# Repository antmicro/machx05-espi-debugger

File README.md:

# MachXO5 eSPI Debugger

Copyright (c) 2026 [Antmicro](https://www.antmicro.com)

## Overview

This project contains open hardware design files for an FPGA-based debug board built around the Lattice MachXO5-NX FPGA.
The board is designed to aid the process of development, bring-up and integration of eSPI-based connections to Data Center Secure Control Modules (DC-SCMs).
It provides USB-accessible UART and JTAG interfaces and a Port 80 status display, enabling development, testing and debugging of eSPI communication before integration into a target server platform.
This project includes only PCB design files - as dedicated bitstream needs to be generated for the on-board Lattice FPGA in order to make it work.
The PCB design files were prepared in KiCad 10.x.

## Key features

* Lattice [MachXO5-NX LFMXO5-25-7BBG400C](https://www.latticesemi.com/en/Products/FPGAandCPLD/MachXO5-NX) FPGA
* Generic 0.1 inch pinhead connector for interfacing with HPM subsystem
* USB-C port with FTDI FT2232H USB interface bridge
* UART and JTAG interfaces accessible from the USB interface bridge
* Port 80 status display with LED indicators
* 125 MHz on-board clock source
* 62 x 87 mm (2.44 x 3.42 inch) PCB outline

## Project structure

The main directory contains KiCad PCB project files, the LICENSE, and this README, and the img directory contains graphics for this README.

## License

This project is licensed under the [Apache-2.0](LICENSE) license.

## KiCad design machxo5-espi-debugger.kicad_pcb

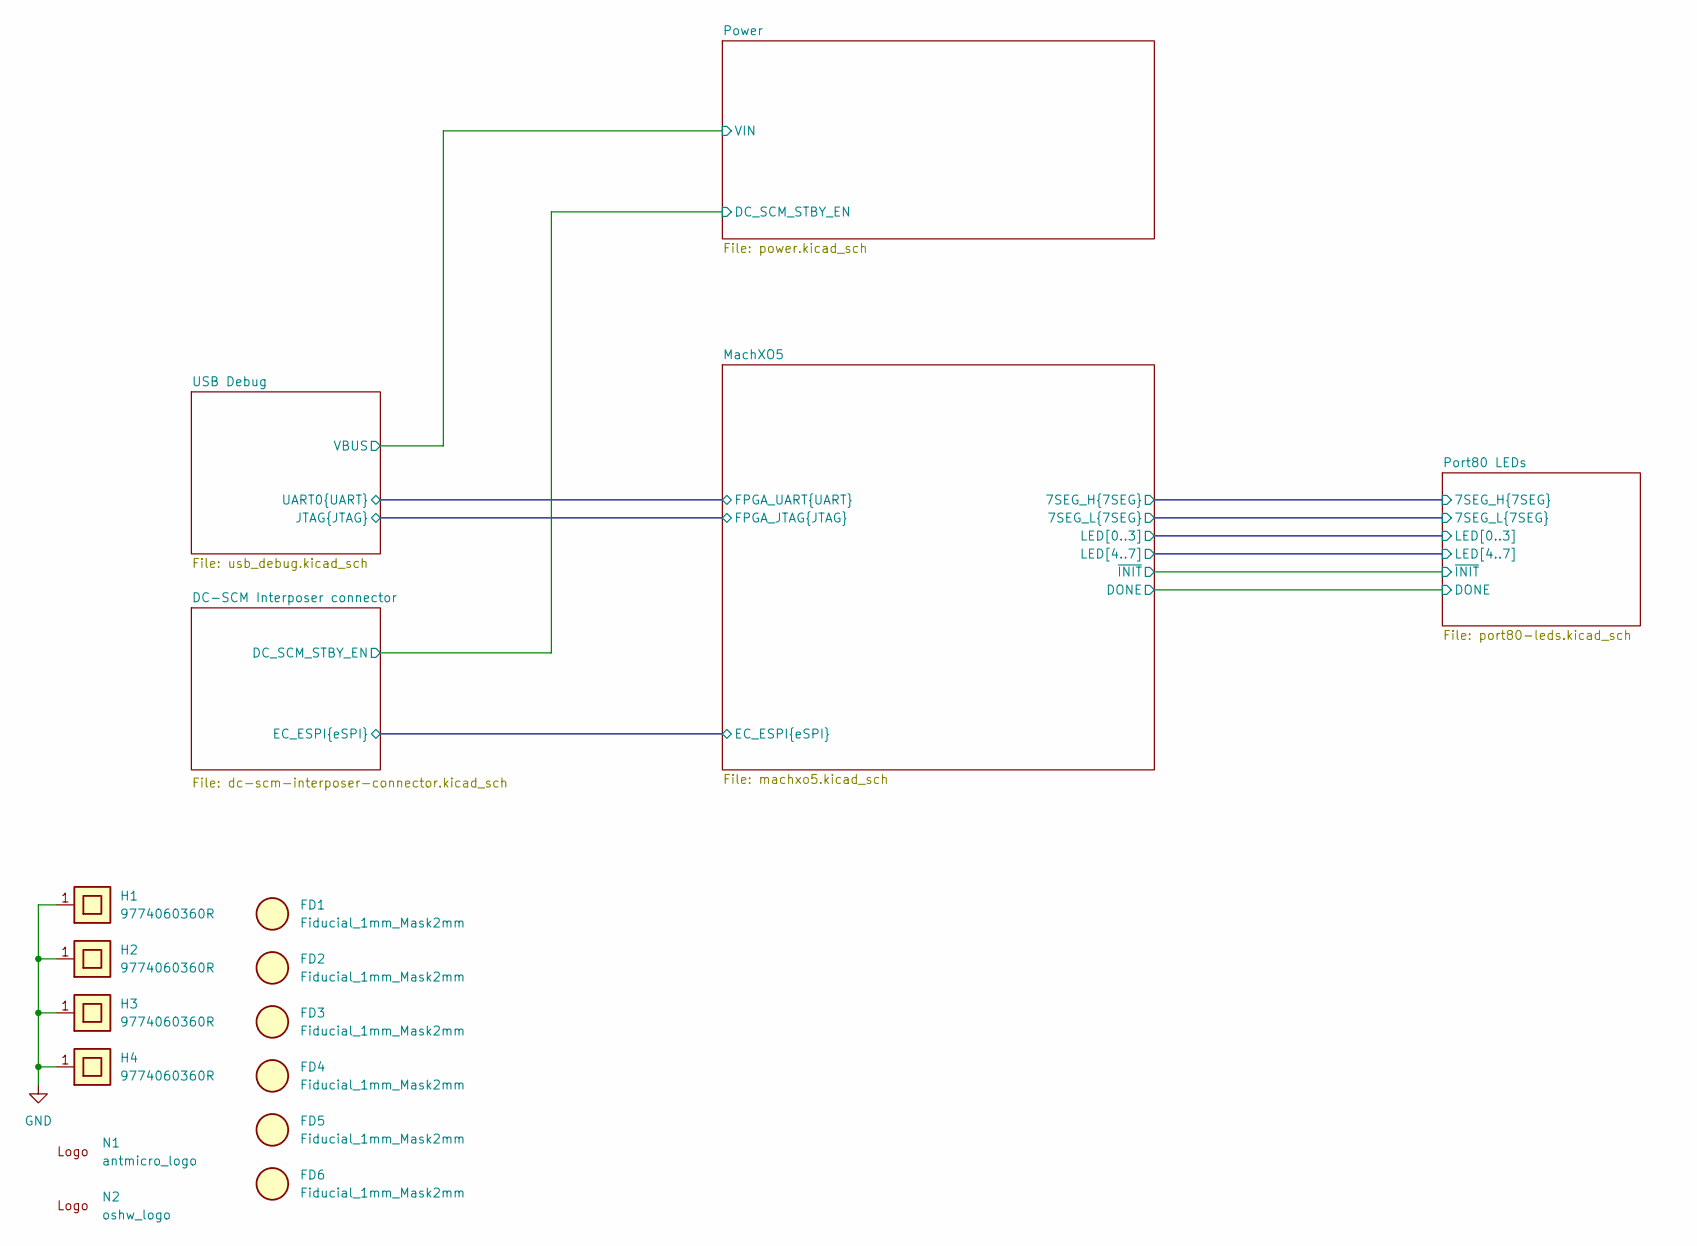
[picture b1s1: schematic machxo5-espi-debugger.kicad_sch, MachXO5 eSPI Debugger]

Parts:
FD1, FD2, FD3, FD4, FD5, FD6: Fiducial_1mm_Mask2mm
H1, H2, H3, H4: Spacer_Drill4.4mm_H6mm_9774060360R; MPN 9774060360R
N1: antmicro_logo; antmicro-logo_scaled_12mm
N2: oshw_logo; oshw-logo

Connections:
GND: H1.1, H2.1, H3.1, H4.1; also elsewhere on the board

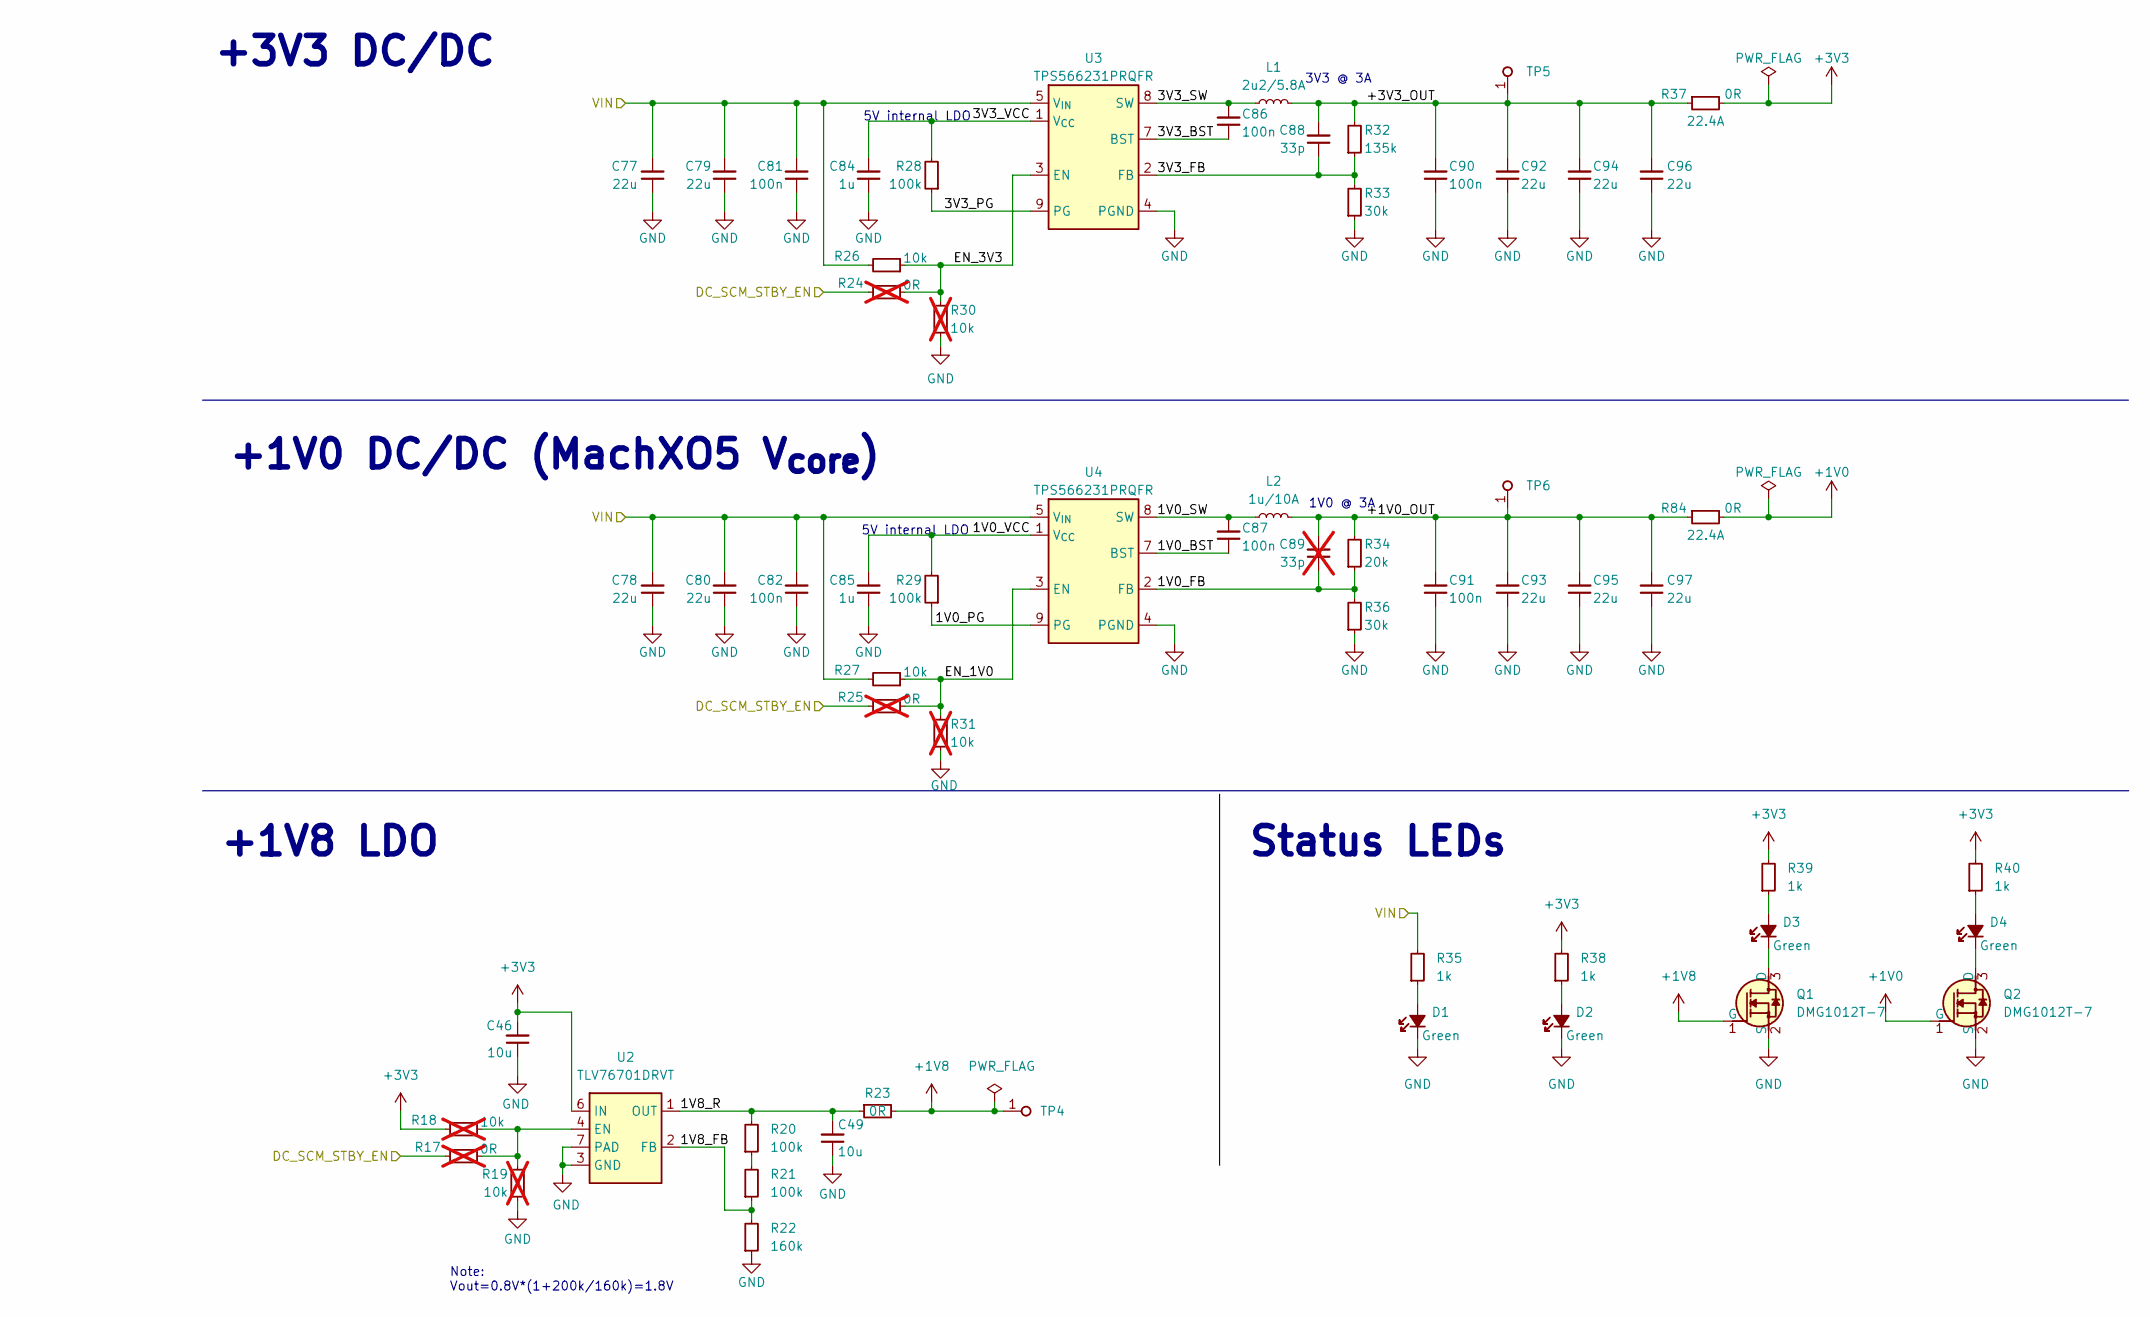
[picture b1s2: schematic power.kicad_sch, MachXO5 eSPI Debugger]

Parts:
C46, C49: C_10u_10V_0402; C_0402_1005Metric; Voltage 10V; MPN GRM155R61A106ME11D
C77, C78, C79, C80, C92, C93, C94, C95, C96, C97: C_22u_16V_0603; C_0603_1608Metric_EIA; Voltage 16V; MPN CL10A226MO7JZNC
C81, C82, C86, C87, C90, C91: C_100n_0402; C_0402_1005Metric; Voltage 50V; MPN GRM155R61H104KE14D
C84, C85: C_1u_25V_0402; C_0402_1005Metric; Voltage 25V; MPN GRM155R61E105KE11J
C88: C_33p_0402; C_0402_1005Metric; MPN 04025A330FAT2A
C89: C_33p_0402; C_0402_1005Metric; MPN 04025A330FAT2A; not fitted
D1, D2, D3, D4: LED_G_0603_LTST-C190GKT; LED_0603_1608Metric_G; MPN LTST-C190GKT
L1: L_2u2_5.8A_WE-PMFI-35329222; L_WE-PMFI-353220; MPN 74479335329222
L2: L_1u_10A_Bourns-SRP4021HMT; L_Bourns-SRP4021HMT; MPN SRP4021HMT-1R0M
Q1, Q2: DMG1012T-7; SOT-523; MPN DMG1012T-7
R17, R24, R25: R_0R_0402; R_0402_1005Metric; MPN ERJ2GE0R00X; not fitted
R18, R19, R30, R31: R_10k_0402; R_0402_1005Metric; Tolerance 1%; MPN CR0402-FX-1002GLF; not fitted
R20, R21, R28, R29: R_100k_0402; R_0402_1005Metric; Tolerance 1%; MPN CR0402-FX-1003GLF
R22: R_160k_0402; R_0402_1005Metric; Tolerance 1%; MPN CR0402-FX-1603GLF
R23: R_0R_0402; R_0402_1005Metric; MPN ERJ2GE0R00X
R26, R27: R_10k_0402; R_0402_1005Metric; Tolerance 1%; MPN CR0402-FX-1002GLF
R32: R_135k_0402; R_0402_1005Metric; Tolerance 0.1%; MPN RT0805BRD07135KL
R33, R36: R_30k_0402; R_0402_1005Metric; Tolerance 1%; MPN CR0402-FX-3002GLF
R34: R_20k_0402; R_0402_1005Metric; Tolerance 1%; MPN CR0402-FX-2002GLF
R35, R38, R39, R40: R_1k_0402; R_0402_1005Metric; Tolerance 1%; MPN CR0402-FX-1001GLF
R37, R84: R_0R_22.4A_0603; R_0603_1608Metric; Tolerance template_tolerance; MPN PMR03EZPJ000
TP4, TP5, TP6: TP_0.75mm_SMD; TP_SMD_0.75mm
U2: TLV76701_WSON; WSON-6-1EP_2x2mm_P0.65mm; MPN TLV76701DRVT
U3, U4: TPS566231P; VQFN-HR-9_2x1.5mm; MPN TPS566231PRQFR

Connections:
+1V0: Q2.1 (G), R84.2; also elsewhere on the board
+1V8: Q1.1 (G), R23.2, TP4.1 (1_1); also elsewhere on the board
+3V3: C46.2, R18.2, R37.2, R38.2, R39.2, R40.2, U2.6 (IN); also elsewhere on the board
/DC-SCM Interposer connector/DC_SCM_STBY_EN: R17.1, R24.1, R25.1; also elsewhere on the board
/Power/1V0_BST: C87.1, U4.7 (BST)
/Power/1V0_FB: C89.1, R34.1, R36.2, U4.2 (FB)
/Power/1V0_PG: R29.1, U4.9 (PG)
/Power/1V0_SW: C87.2, L2.1, U4.8 (SW)
/Power/1V0_VCC: C85.2, R29.2, U4.1 (V_{CC})
/Power/1V8_FB: R21.1, R22.2, U2.2 (FB)
/Power/1V8_R: C49.2, R20.2, R23.1, U2.1 (OUT)
/Power/3V3_BST: C86.1, U3.7 (BST)
/Power/3V3_FB: C88.1, R32.1, R33.2, U3.2 (FB)
/Power/3V3_PG: R28.1, U3.9 (PG)
/Power/3V3_SW: C86.2, L1.1, U3.8 (SW)
/Power/3V3_VCC: C84.2, R28.2, U3.1 (V_{CC})
/Power/+1V0_OUT: C89.2, C91.2, C93.2, C95.2, C97.2, L2.2, R34.2, R84.1, TP6.1 (1_1)
/Power/+3V3_OUT: C88.2, C90.2, C92.2, C94.2, C96.2, L1.2, R32.2, R37.1, TP5.1 (1_1)
/Power/EN_1V0: R25.2, R27.1, R31.2, U4.3 (EN)
/Power/EN_3V3: R24.2, R26.1, R30.2, U3.3 (EN)
/Power/VIN: C77.2, C78.2, C79.2, C80.2, C81.2, C82.2, R26.2, R27.2, R35.2, U3.5 (V_{IN}), U3.6 (V_{IN}), U4.5 (V_{IN}), U4.6 (V_{IN}); also elsewhere on the board
GND: C46.1, C49.1, C77.1, C78.1, C79.1, C80.1, C81.1, C82.1, C84.1, C85.1, C90.1, C91.1, C92.1, C93.1, C94.1, C95.1, C96.1, C97.1, D1.1 (C), D2.1 (C), Q1.2 (S), Q2.2 (S), R19.1, R22.1, R30.1, R31.1, R33.1, R36.1, U2.3 (GND), U2.5 (GND), U2.7 (PAD), U3.4 (PGND), U4.4 (PGND); also elsewhere on the board
unnamed: D1.2 (A), R35.1
unnamed: D2.2 (A), R38.1
unnamed: D3.2 (A), R39.1
unnamed: D3.1 (C), Q1.3 (D)
unnamed: D4.2 (A), R40.1
unnamed: D4.1 (C), Q2.3 (D)
unnamed: R20.1, R21.2
unnamed: R17.2, R18.1, R19.2, U2.4 (EN)

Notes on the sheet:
5V internal LDO
Note: Vout=0.8V*(1+200k/160k)=1.8V
3V3 @ 3A
Status LEDs
+1V8 LDO
1V0 @ 3A
+1V0 DC/DC (MachXO5 V_{core})
+3V3 DC/DC

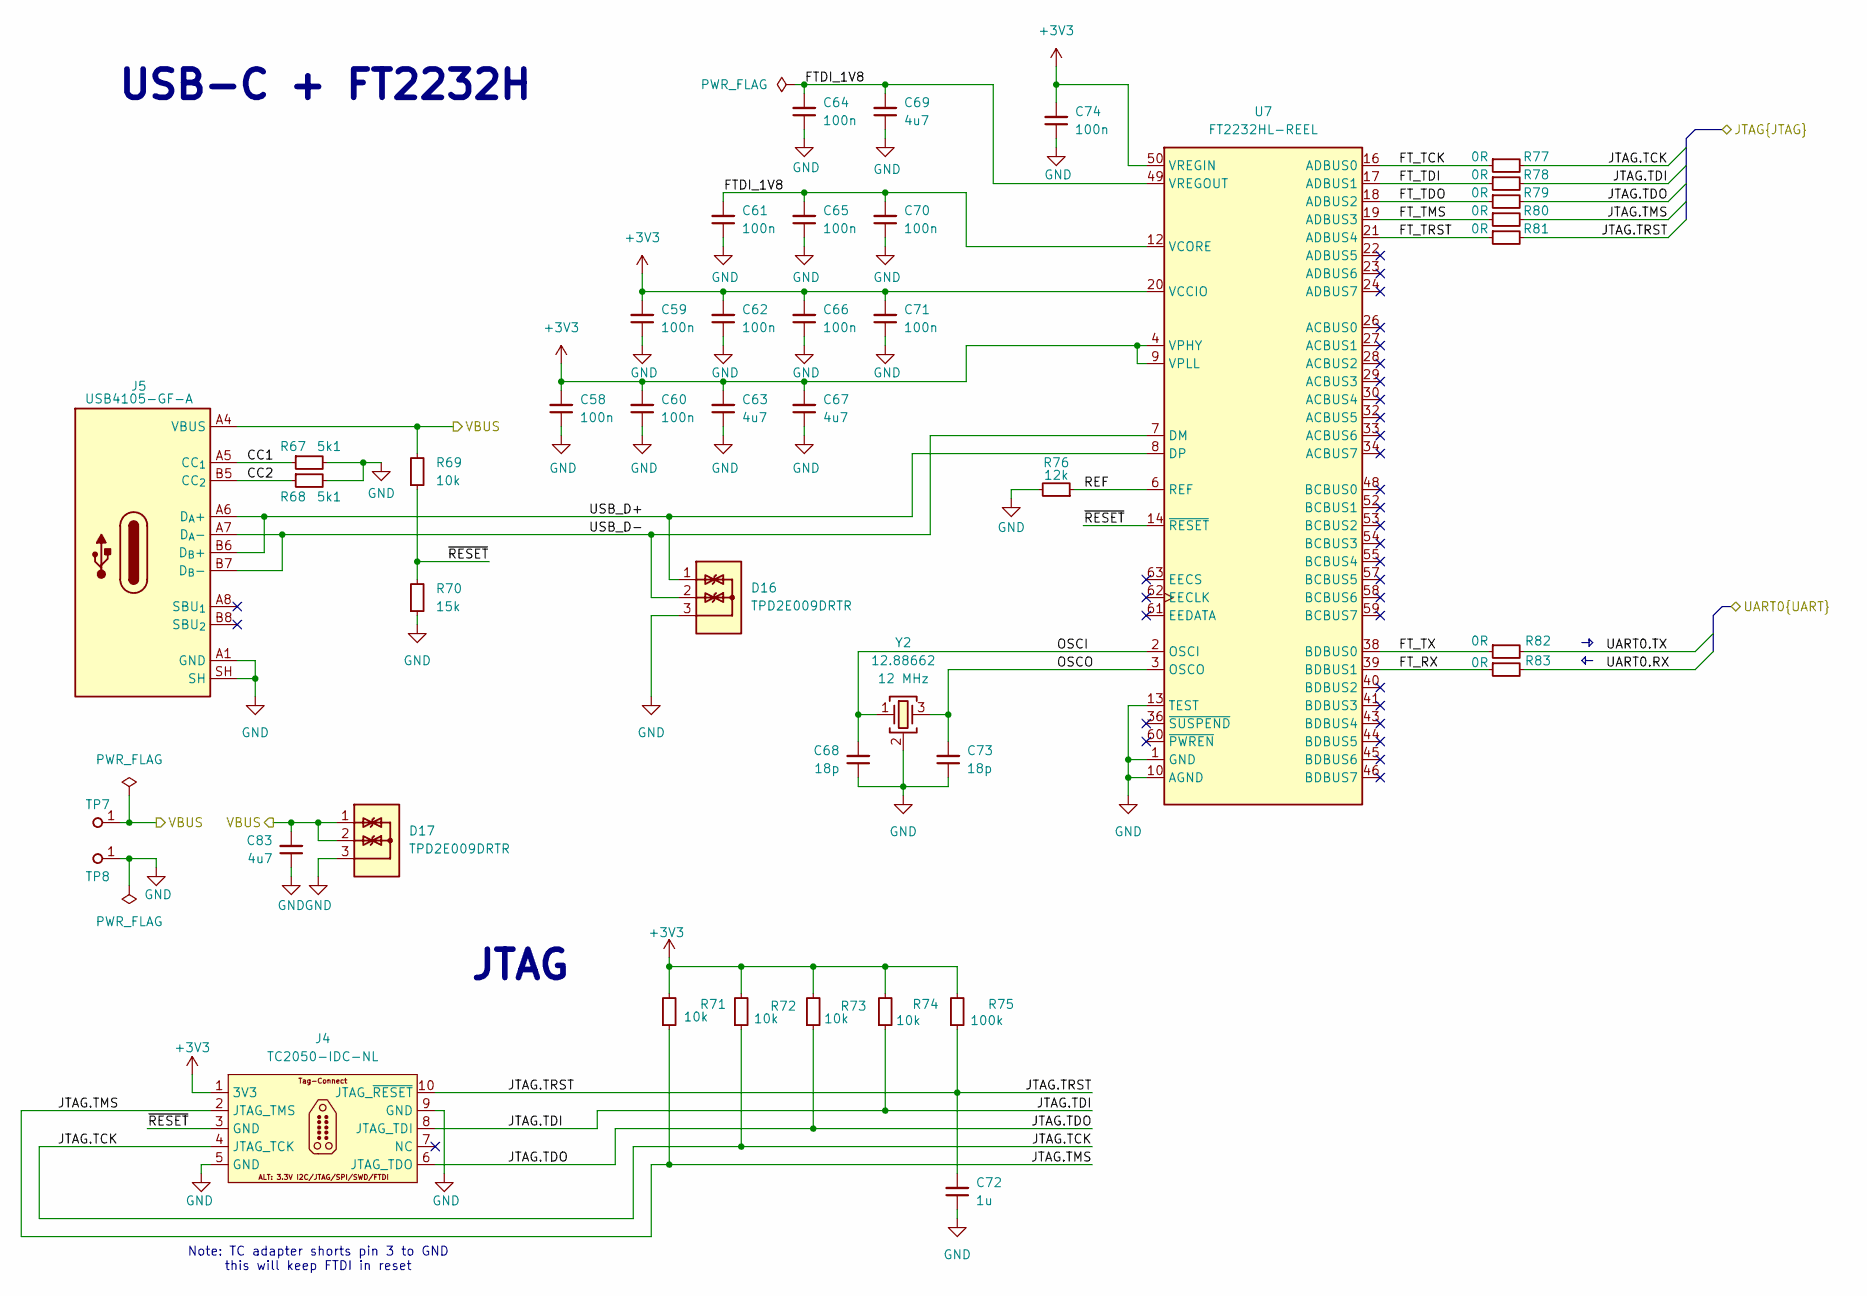
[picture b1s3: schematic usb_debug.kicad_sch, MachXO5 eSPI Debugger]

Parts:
C58, C59, C60, C61, C62, C64, C65, C66, C70, C71, C74: C_100n_16V_X7R_0402; C_0402_1005Metric; Voltage 16V; MPN C0402C104J4RAC7411
C63, C67, C69, C83: C_4u7_10V_X7T_0402; C_0402_1005Metric; Voltage 10V; MPN GRM155D71A475ME15D
C68, C73: C_18p_0402; C_0402_1005Metric; MPN CL05C180JB51PNC
C72: C_1u_0402; C_0402_1005Metric; MPN C1005X6S1A105K050BC
D16, D17: TPD2E009_SOT-9X3; SOT-723; MPN TPD2E009DRTR
J4: Tag-Connect_TC2050-IDC-NL_2x5_P1.27mm; MPN TC2050-IDC-NL
J5: USB-C_GCT_USB4105-GF-A; USB-C_Receptacle_GCT_USB4105-GF-A; MPN USB4105-GF-A
R67, R68: R_5k1_0402; R_0402_1005Metric; Tolerance 1%; MPN CR0402-FX-5101GLF
R69, R71, R72, R73, R74: R_10k_0402; R_0402_1005Metric; Tolerance 1%; MPN CR0402-FX-1002GLF
R70: R_15k_0402; R_0402_1005Metric; Tolerance 1%; MPN CR0402-FX-1502GLF
R75: R_100k_0402; R_0402_1005Metric; Tolerance 1%; MPN CR0402-FX-1003GLF
R76: R_12k_0402; R_0402_1005Metric; Tolerance 1%; MPN CR0402-FX-1202GLF
R77, R78, R79, R80, R81, R82, R83: R_0R_0402; R_0402_1005Metric; MPN ERJ2GE0R00X
TP7, TP8: TP_1mm_SMD; TP_SMD_1mm
U7: FT2232HL-REEL; LQFP-64_10x10mm_P0.5mm; MPN FT2232HL-REEL
Y2: Resonator_12MHz_KX-7; Resonator_SMD_Geyer_KX-7_3.2x2.5x0.8mm; MPN 12.88662

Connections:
+3V3: C58.2, C59.2, C60.2, C62.2, C63.2, C66.2, C67.2, C71.2, C74.2, J4.1, R71.2, R72.2, R73.2, R74.2, R75.2, U7.4 (VPHY), U7.9 (VPLL), U7.20 (VCCIO), U7.31 (VCCIO), U7.42 (VCCIO), U7.50 (VREGIN), U7.56 (VCCIO); also elsewhere on the board
/MachXO5/FPGA_JTAG.TCK: J4.4, R72.1, R77.2; also elsewhere on the board
/MachXO5/FPGA_JTAG.TDI: J4.8, R74.1, R78.2; also elsewhere on the board
/MachXO5/FPGA_JTAG.TDO: J4.6, R73.1, R79.2; also elsewhere on the board
/MachXO5/FPGA_JTAG.TMS: J4.2, R71.1, R80.2; also elsewhere on the board
/MachXO5/FPGA_JTAG.TRST: C72.2, J4.10, R75.1, R81.2; also elsewhere on the board
/MachXO5/FPGA_UART.RX: R83.2; also elsewhere on the board
/MachXO5/FPGA_UART.TX: R82.2; also elsewhere on the board
/Power/VIN: C83.2, D17.1, D17.2, J5.A4 (VBUS), J5.A9 (VBUS), J5.B4 (VBUS), J5.B9 (VBUS), R69.2, TP7.1 (1_1); also elsewhere on the board
/USB Debug/CC1: J5.A5 (CC_{1}), R67.1
/USB Debug/CC2: J5.B5 (CC_{2}), R68.1
/USB Debug/FTDI_1V8: C61.2, C64.2, C65.2, C69.2, C70.2, U7.12 (VCORE), U7.37 (VCORE), U7.49 (VREGOUT), U7.64 (VCORE)
/USB Debug/FT_RX: R83.1, U7.39 (BDBUS1)
/USB Debug/FT_TCK: R77.1, U7.16 (ADBUS0)
/USB Debug/FT_TDI: R78.1, U7.17 (ADBUS1)
/USB Debug/FT_TDO: R79.1, U7.18 (ADBUS2)
/USB Debug/FT_TMS: R80.1, U7.19 (ADBUS3)
/USB Debug/FT_TRST: R81.1, U7.21 (ADBUS4)
/USB Debug/FT_TX: R82.1, U7.38 (BDBUS0)
/USB Debug/OSCI: C68.2, U7.2 (OSCI), Y2.1
/USB Debug/OSCO: C73.2, U7.3 (OSCO), Y2.3
/USB Debug/REF: R76.1, U7.6 (REF)
/USB Debug/USB_D+: D16.1, J5.A6 (D_{A}+), J5.B6 (D_{B}+), U7.8 (DP)
/USB Debug/USB_D-: D16.2, J5.A7 (D_{A}-), J5.B7 (D_{B}-), U7.7 (DM)
/USB Debug/~RESET: J4.3, R69.1, R70.2, U7.14 (~RESET)
GND: C58.1, C59.1, C60.1, C61.1, C62.1, C63.1, C64.1, C65.1, C66.1, C67.1, C68.1, C69.1, C70.1, C71.1, C72.1, C73.1, C74.1, C83.1, D16.3, D17.3, J4.5, J4.9, J5.A1 (GND), J5.A12 (GND), J5.B1 (GND), J5.B12 (GND), J5.SH, R67.2, R68.2, R70.1, R76.2, TP8.1 (1_1), U7.1 (GND), U7.5 (GND), U7.10 (AGND), U7.11 (GND), U7.13 (TEST), U7.15 (GND), U7.25 (GND), U7.35 (GND), U7.47 (GND), U7.51 (GND), Y2.2 (SH), Y2.4 (SH); also elsewhere on the board

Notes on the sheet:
JTAG
USB-C + FT2232H
Note: TC adapter shorts pin 3 to GND this will keep FTDI in reset

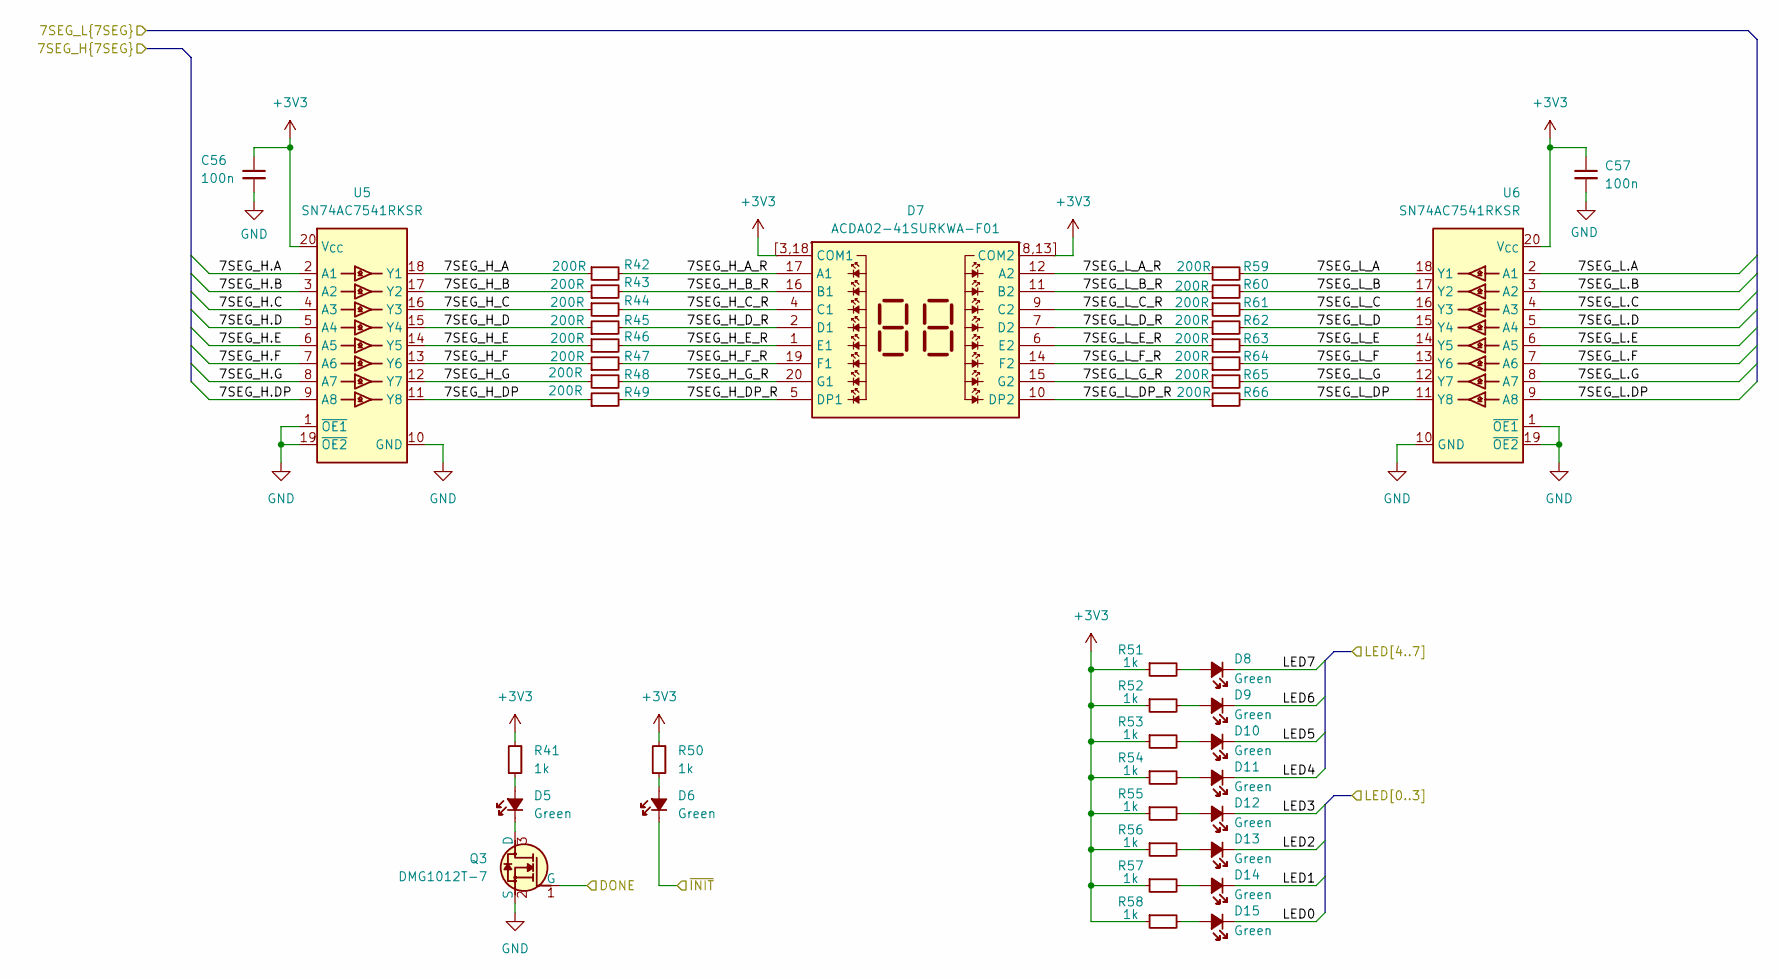
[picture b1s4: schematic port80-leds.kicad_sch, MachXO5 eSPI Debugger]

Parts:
C56, C57: C_100n_0402; C_0402_1005Metric; Voltage 50V; MPN GRM155R61H104KE14D
D5, D6, D8, D9, D10, D11, D12, D13, D14, D15: LED_G_0603_LTST-C190GKT; LED_0603_1608Metric_G; MPN LTST-C190GKT
D7: ACDA02-41SURKWA-F01; MPN ACDA02-41SURKWA-F01
Q3: DMG1012T-7; SOT-523; MPN DMG1012T-7
R41, R50, R51, R52, R53, R54, R55, R56, R57, R58: R_1k_0402; R_0402_1005Metric; Tolerance 1%; MPN CR0402-FX-1001GLF
R42, R43, R44, R45, R46, R47, R48, R49, R59, R60, R61, R62, R63, R64, R65, R66: R_200R_0402; R_0402_1005Metric; Tolerance 1%; MPN CR0402-FX-2000GLF
U5, U6: SN74AC7541_VQFN; VQFN-20_1EP_4.5x2.5mm_P0.5mm; MPN SN74AC7541RKSR

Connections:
+3V3: C56.1, C57.1, D7.3 (COM1), D7.8 (COM2), D7.13 (COM2), D7.18 (COM1), D7.[3,18] (COM1), D7.[8,13] (COM2), R41.2, R50.2, R51.1, R52.1, R53.1, R54.1, R55.1, R56.1, R57.1, R58.1, U5.20 (V_{CC}), U6.20 (V_{CC}); also elsewhere on the board
/MachXO5/7SEG_H.A: U5.2 (A1); also elsewhere on the board
/MachXO5/7SEG_H.B: U5.3 (A2); also elsewhere on the board
/MachXO5/7SEG_H.C: U5.4 (A3); also elsewhere on the board
/MachXO5/7SEG_H.D: U5.5 (A4); also elsewhere on the board
/MachXO5/7SEG_H.DP: U5.9 (A8); also elsewhere on the board
/MachXO5/7SEG_H.E: U5.6 (A5); also elsewhere on the board
/MachXO5/7SEG_H.F: U5.7 (A6); also elsewhere on the board
/MachXO5/7SEG_H.G: U5.8 (A7); also elsewhere on the board
/MachXO5/7SEG_L.A: U6.2 (A1); also elsewhere on the board
/MachXO5/7SEG_L.B: U6.3 (A2); also elsewhere on the board
/MachXO5/7SEG_L.C: U6.4 (A3); also elsewhere on the board
/MachXO5/7SEG_L.D: U6.5 (A4); also elsewhere on the board
/MachXO5/7SEG_L.DP: U6.9 (A8); also elsewhere on the board
/MachXO5/7SEG_L.E: U6.6 (A5); also elsewhere on the board
/MachXO5/7SEG_L.F: U6.7 (A6); also elsewhere on the board
/MachXO5/7SEG_L.G: U6.8 (A7); also elsewhere on the board
/MachXO5/DONE: Q3.1 (G); also elsewhere on the board
/MachXO5/LED0: D15.1 (C); also elsewhere on the board
/MachXO5/LED1: D14.1 (C); also elsewhere on the board
/MachXO5/LED2: D13.1 (C); also elsewhere on the board
/MachXO5/LED3: D12.1 (C); also elsewhere on the board
/MachXO5/LED4: D11.1 (C); also elsewhere on the board
/MachXO5/LED5: D10.1 (C); also elsewhere on the board
/MachXO5/LED6: D9.1 (C); also elsewhere on the board
/MachXO5/LED7: D8.1 (C); also elsewhere on the board
/MachXO5/~INIT: D6.1 (C); also elsewhere on the board
/Port80 LEDs/7SEG_H_A: R42.1, U5.18 (Y1)
/Port80 LEDs/7SEG_H_A_R: D7.17 (A1), R42.2
/Port80 LEDs/7SEG_H_B: R43.1, U5.17 (Y2)
/Port80 LEDs/7SEG_H_B_R: D7.16 (B1), R43.2
/Port80 LEDs/7SEG_H_C: R44.1, U5.16 (Y3)
/Port80 LEDs/7SEG_H_C_R: D7.4 (C1), R44.2
/Port80 LEDs/7SEG_H_D: R45.1, U5.15 (Y4)
/Port80 LEDs/7SEG_H_DP: R49.1, U5.11 (Y8)
/Port80 LEDs/7SEG_H_DP_R: D7.5 (DP1), R49.2
/Port80 LEDs/7SEG_H_D_R: D7.2 (D1), R45.2
/Port80 LEDs/7SEG_H_E: R46.1, U5.14 (Y5)
/Port80 LEDs/7SEG_H_E_R: D7.1 (E1), R46.2
/Port80 LEDs/7SEG_H_F: R47.1, U5.13 (Y6)
/Port80 LEDs/7SEG_H_F_R: D7.19 (F1), R47.2
/Port80 LEDs/7SEG_H_G: R48.1, U5.12 (Y7)
/Port80 LEDs/7SEG_H_G_R: D7.20 (G1), R48.2
/Port80 LEDs/7SEG_L_A: R59.2, U6.18 (Y1)
/Port80 LEDs/7SEG_L_A_R: D7.12 (A2), R59.1
/Port80 LEDs/7SEG_L_B: R60.2, U6.17 (Y2)
/Port80 LEDs/7SEG_L_B_R: D7.11 (B2), R60.1
/Port80 LEDs/7SEG_L_C: R61.2, U6.16 (Y3)
/Port80 LEDs/7SEG_L_C_R: D7.9 (C2), R61.1
/Port80 LEDs/7SEG_L_D: R62.2, U6.15 (Y4)
/Port80 LEDs/7SEG_L_DP: R66.2, U6.11 (Y8)
/Port80 LEDs/7SEG_L_DP_R: D7.10 (DP2), R66.1
/Port80 LEDs/7SEG_L_D_R: D7.7 (D2), R62.1
/Port80 LEDs/7SEG_L_E: R63.2, U6.14 (Y5)
/Port80 LEDs/7SEG_L_E_R: D7.6 (E2), R63.1
/Port80 LEDs/7SEG_L_F: R64.2, U6.13 (Y6)
/Port80 LEDs/7SEG_L_F_R: D7.14 (F2), R64.1
/Port80 LEDs/7SEG_L_G: R65.2, U6.12 (Y7)
/Port80 LEDs/7SEG_L_G_R: D7.15 (G2), R65.1
GND: C56.2, C57.2, Q3.2 (S), U5.1 (~OE1), U5.10 (GND), U5.19 (~OE2), U5.21 (GND), U6.1 (~OE1), U6.10 (GND), U6.19 (~OE2), U6.21 (GND); also elsewhere on the board
unnamed: D5.2 (A), R41.1
unnamed: D5.1 (C), Q3.3 (D)
unnamed: D6.2 (A), R50.1
unnamed: D8.2 (A), R51.2
unnamed: D9.2 (A), R52.2
unnamed: D10.2 (A), R53.2
unnamed: D11.2 (A), R54.2
unnamed: D12.2 (A), R55.2
unnamed: D13.2 (A), R56.2
unnamed: D14.2 (A), R57.2
unnamed: D15.2 (A), R58.2

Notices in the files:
parts and their libraries:
License: Apache-2.0
